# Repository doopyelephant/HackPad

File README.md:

# HackPad
A 16 Key HackPad with a salvaged Touchpad used for swipe gestures, and moving around 3D software, uses QMK Firmware.
## Features:
- 16 Keys
- ELAN Touchpad
- 3D Printed Case
## CAD Model:
It all fits together with 4x M3x16mm screws, one in each corner of the case to connect the bottom to the top, the PCB will just be sandwiched between the bottom and top. There are 2 printed pieces, the "lid" with key holes and bottom.

## PCB:
This is the PCB! It has the microcontroller along with 16 key switches in a matrix. 

Aswell as a place to solder on the 12 pin FFC(Flat Flexible Connecter) that connects to the touchpad. The pinout of the touchpad was reverse engineered with a multimeter and a few partial labels on the donor board, I believe the touchpad uses the PS/2 protocol(the circular mouse port from the 90s) with a few modifications:

-  FFC instead of circular port
- The Two extra pins in the spec are used to relay LB and RB through the touchpad like: LB & RB -> Touchpad -> SOC

## Firmware
This Hackpad uses QMK (QMK suprisingly has support for PS/2! )

- Keys can be programmed to whatever, defaults to a numpad
- Touchpad acts as a mouse, planning on making a userspace driver to do more fancy things in the future

Thats it for now!

## BOM:
- 4x M3x16mm screws
- 16x 1N4148 Diodes
- 16x DSA Keycaps
- 16x Cherry MX Switches
- 1x XIAO RP2040
- 1x Case (2 Printed Parts)

  **Already Obtained:**
- 1x 12 pin FFC connector (I salvaged this from the main PCB on the same broken keyboard mentioned below)
- 1x ELAN CK77 Touchpad (I already Salvaged this from a broken keyboard, you might be able to find one to, they are pretty old and are in various things, mine was designed in 2007)

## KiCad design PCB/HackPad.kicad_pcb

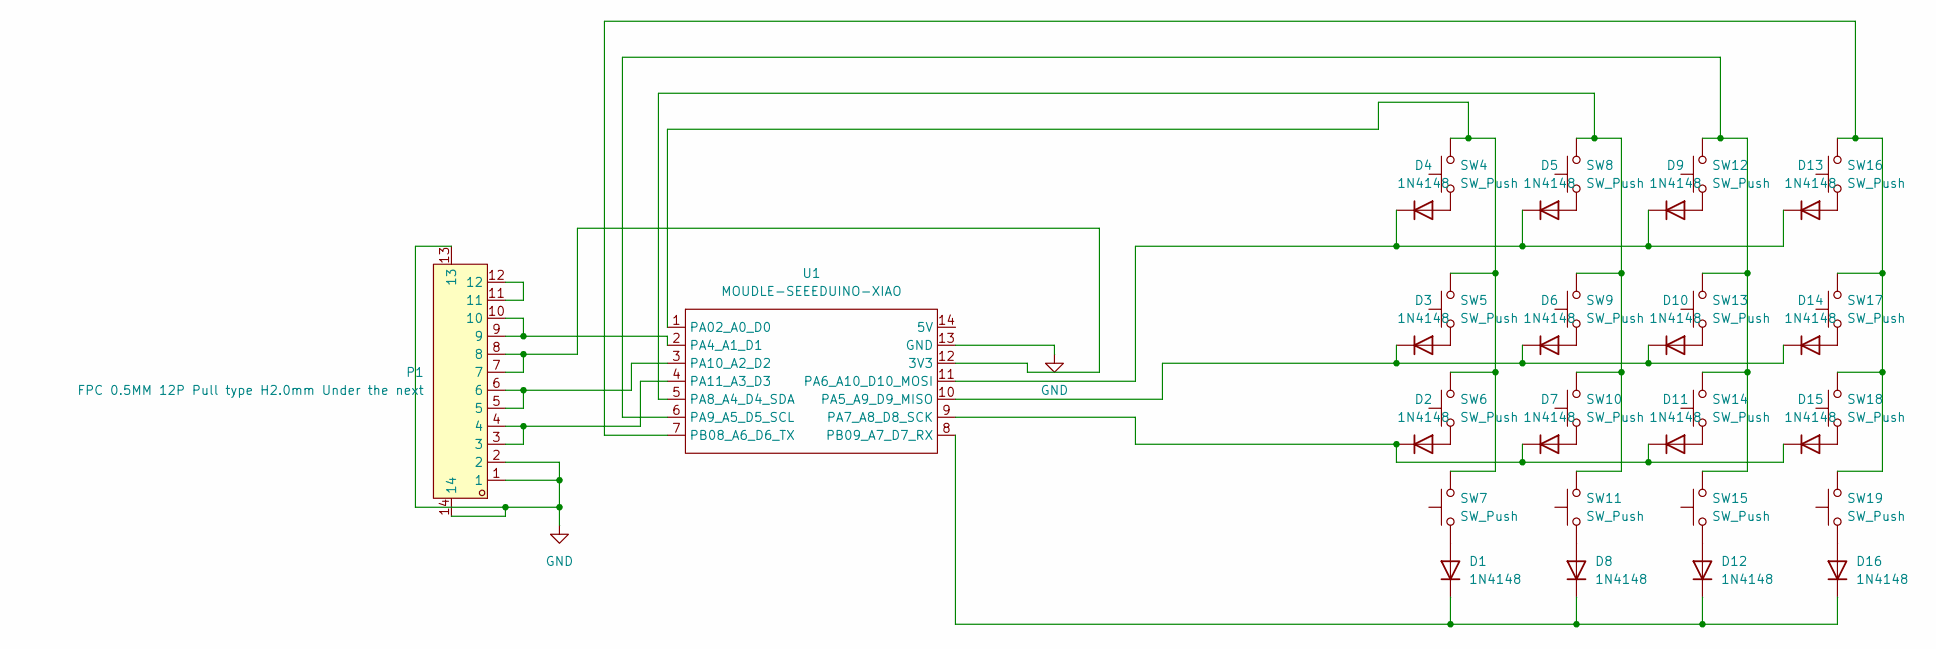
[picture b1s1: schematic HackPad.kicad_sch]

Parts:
D1, D2, D3, D4, D5, D6, D7, D8, D9, D10, D11, D12, D13, D14, D15, D16: 1N4148; D_DO-35_SOD27_P7.62mm_Horizontal
P1: FPC 0.5MM 12P Pull type H2.0mm Under the next; FPC-SMD_12P-P0.50_AFC07-S12FCC-00; MPN AFC07-S12FCC-00; LCSC Part C11051
SW4, SW5, SW6, SW7, SW8, SW9, SW10, SW11, SW12, SW13, SW14, SW15, SW16, SW17, SW18, SW19: SW_Push; SW_Cherry_MX_1.00u_PCB
U1: MOUDLE-SEEEDUINO-XIAO; XIAO-Generic-Hybrid-14P-2.54-21X17.8MM

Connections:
GND: P1.1, P1.2, P1.13, P1.14, U1.13 (GND)
unnamed: D1.2 (A), SW7.1
unnamed: D1.1 (K), D8.1 (K), D12.1 (K), D16.1 (K), U1.8 (PB09_A7_D7_RX)
unnamed: D2.2 (A), SW6.1
unnamed: D3.2 (A), SW5.1
unnamed: D4.2 (A), SW4.1
unnamed: D5.2 (A), SW8.1
unnamed: D6.2 (A), SW9.1
unnamed: D7.2 (A), SW10.1
unnamed: D8.2 (A), SW11.1
unnamed: D9.2 (A), SW12.1
unnamed: D10.2 (A), SW13.1
unnamed: D3.1 (K), D6.1 (K), D10.1 (K), D14.1 (K), U1.10 (PA5_A9_D9_MISO)
unnamed: D11.2 (A), SW14.1
unnamed: D2.1 (K), D7.1 (K), D11.1 (K), D15.1 (K), U1.9 (PA7_A8_D8_SCK)
unnamed: D12.2 (A), SW15.1
unnamed: D13.2 (A), SW16.1
unnamed: D4.1 (K), D5.1 (K), D9.1 (K), D13.1 (K), U1.11 (PA6_A10_D10_MOSI)
unnamed: D14.2 (A), SW17.1
unnamed: D15.2 (A), SW18.1
unnamed: D16.2 (A), SW19.1
unnamed: P1.11, P1.12
unnamed: P1.7, P1.8, U1.12 (3V3)
unnamed: SW4.2, SW5.2, SW6.2, SW7.2, U1.1 (PA02_A0_D0)
unnamed: P1.9, P1.10, U1.2 (PA4_A1_D1)
unnamed: SW8.2, SW9.2, SW10.2, SW11.2, U1.5 (PA8_A4_D4_SDA)
unnamed: SW12.2, SW13.2, SW14.2, SW15.2, U1.6 (PA9_A5_D5_SCL)
unnamed: P1.5, P1.6, U1.3 (PA10_A2_D2)
unnamed: P1.3, P1.4, U1.4 (PA11_A3_D3)
unnamed: SW16.2, SW17.2, SW18.2, SW19.2, U1.7 (PB08_A6_D6_TX)

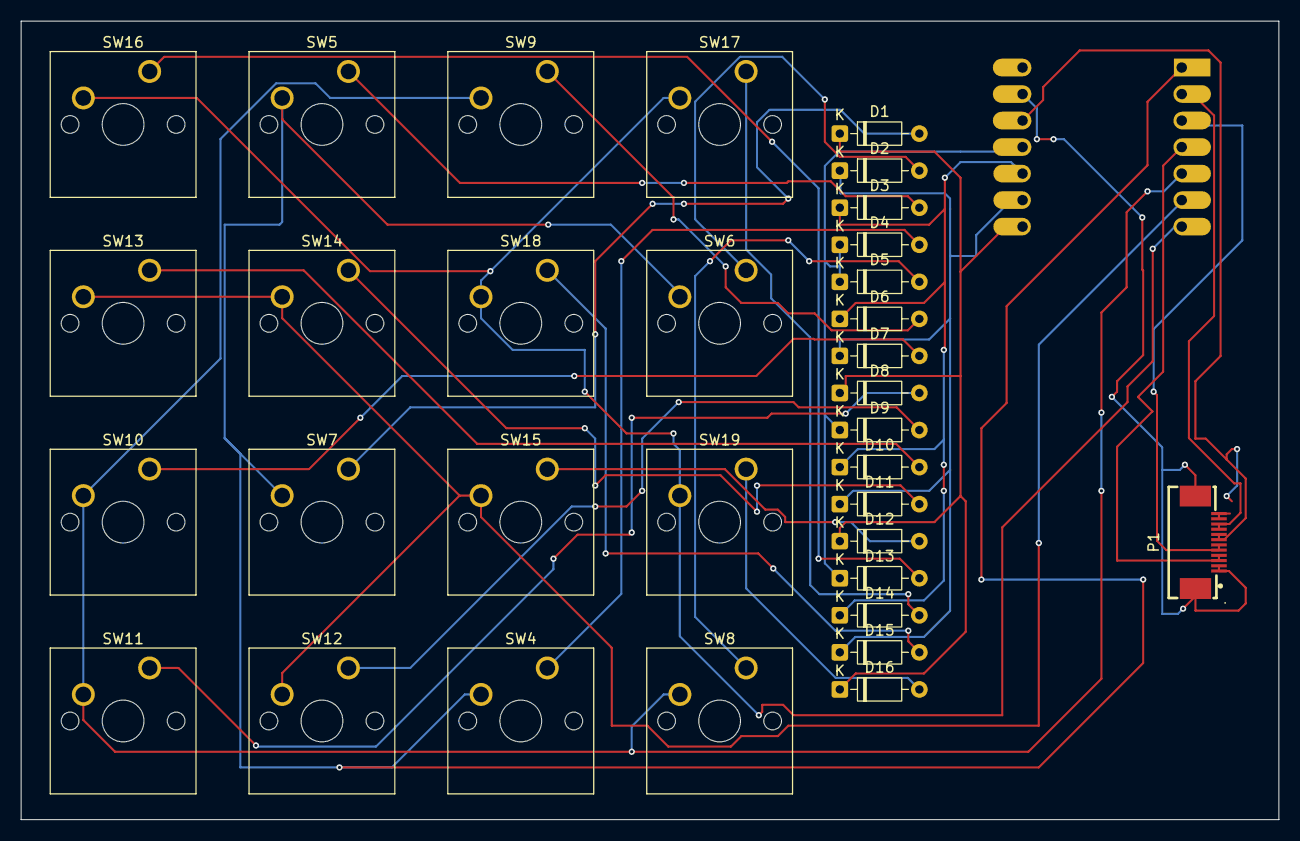
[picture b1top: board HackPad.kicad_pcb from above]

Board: 2 copper layers, 120.5 x 76.5 mm, 34 parts (1 on the bottom side), 30 nets.
